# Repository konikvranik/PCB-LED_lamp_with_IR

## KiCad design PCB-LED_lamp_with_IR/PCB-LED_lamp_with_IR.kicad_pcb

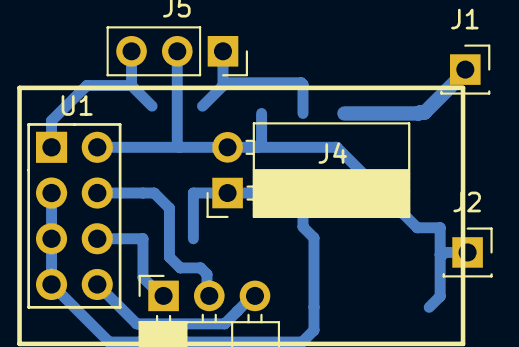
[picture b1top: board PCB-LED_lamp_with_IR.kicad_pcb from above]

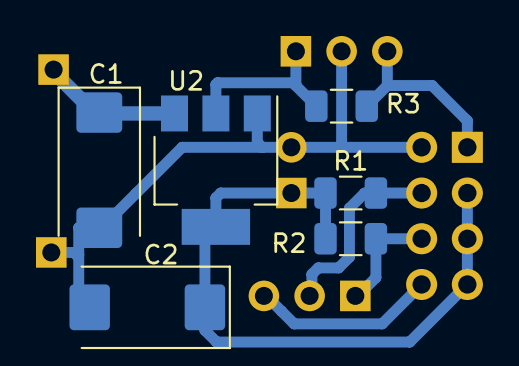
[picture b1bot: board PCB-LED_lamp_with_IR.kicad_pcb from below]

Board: 2 copper layers, 12 parts (6 on the bottom side), 7 nets.

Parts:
C1, C2: 470µ; CP_EIA-7343-31_Kemet-D_Pad2.25x2.55mm_HandSolder
J1: +5V; PinSocket_1x01_P2.54mm_Vertical
J2: GND; PinSocket_1x01_P2.54mm_Vertical
J3: OUTPUTS; PinSocket_1x03_P2.54mm_Horizontal
J4: 3V3 PWR; PinSocket_1x02_P2.54mm_Horizontal
J5: TSOP4836; PinSocket_1x03_P2.54mm_Vertical
R1, R2, R3: 3K3; R_1206_3216Metric
U1: ESP-01v090; ESP-01
U2: AMS1117-3.3; SOT-223-3_TabPin2

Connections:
+3V3: C2.1, J4.1, J5.1, R1.2, R2.1, R3.1, U1.CH_PD, U1.RST, U1.VCC, U2.2
+5V: C1.1, J1.1, U2.3
/IR: J5.3, R3.2, U1.TXD
GNDREF: C1.2, C2.2, J2.1, J4.2, J5.2, U1.GND, U2.1
LEDS1: J3.1, R2.2, U1.GPIO0
LEDS2: J3.2, R1.1, U1.GPIO2
LEDS3: J3.3, U1.RXD

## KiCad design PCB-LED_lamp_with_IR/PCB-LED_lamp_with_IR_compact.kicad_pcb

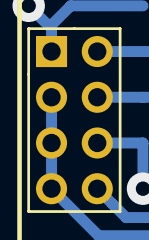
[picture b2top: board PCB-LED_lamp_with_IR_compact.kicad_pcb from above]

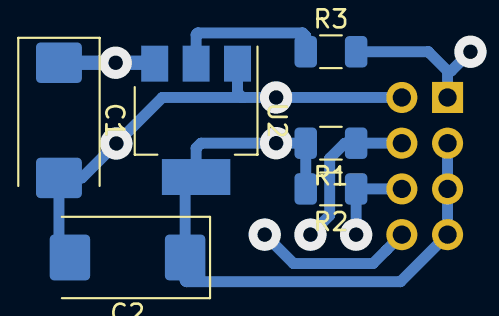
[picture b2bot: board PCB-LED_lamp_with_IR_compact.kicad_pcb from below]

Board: 2 copper layers, 7 parts (6 on the bottom side), 6 nets.

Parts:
C1, C2: 10µ; CP_EIA-7343-31_Kemet-D_Pad2.25x2.55mm_HandSolder
R1, R2: R; R_1206_3216Metric
R3: 3K3; R_1206_3216Metric
U1: ESP-01v090; ESP-01
U2: AMS1117-3.3; SOT-223-3_TabPin2

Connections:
+3V3: C2.1, R1.2, R2.1, R3.1, U1.3, U1.5, U1.7, U2.2
+5V: C1.1, U2.3
GNDREF: C1.2, C2.2, U1.2, U2.1
LEDS1: R3.2, U1.1
LEDS2: R1.1, U1.4
LEDS3: R2.2, U1.6

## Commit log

2019-10-21 lampicka
2019-10-21 lampickaIR
2019-10-29 pcb transistors
2019-10-29 IR + SOT transistors
2019-11-04 no 10k resistors
2019-11-06 no 10k resistors routed
2019-11-17 addressable
2020-02-13 kikcad
2020-02-13 lamp
2020-02-14 leds
2020-02-15 settings
2020-02-15 pins
